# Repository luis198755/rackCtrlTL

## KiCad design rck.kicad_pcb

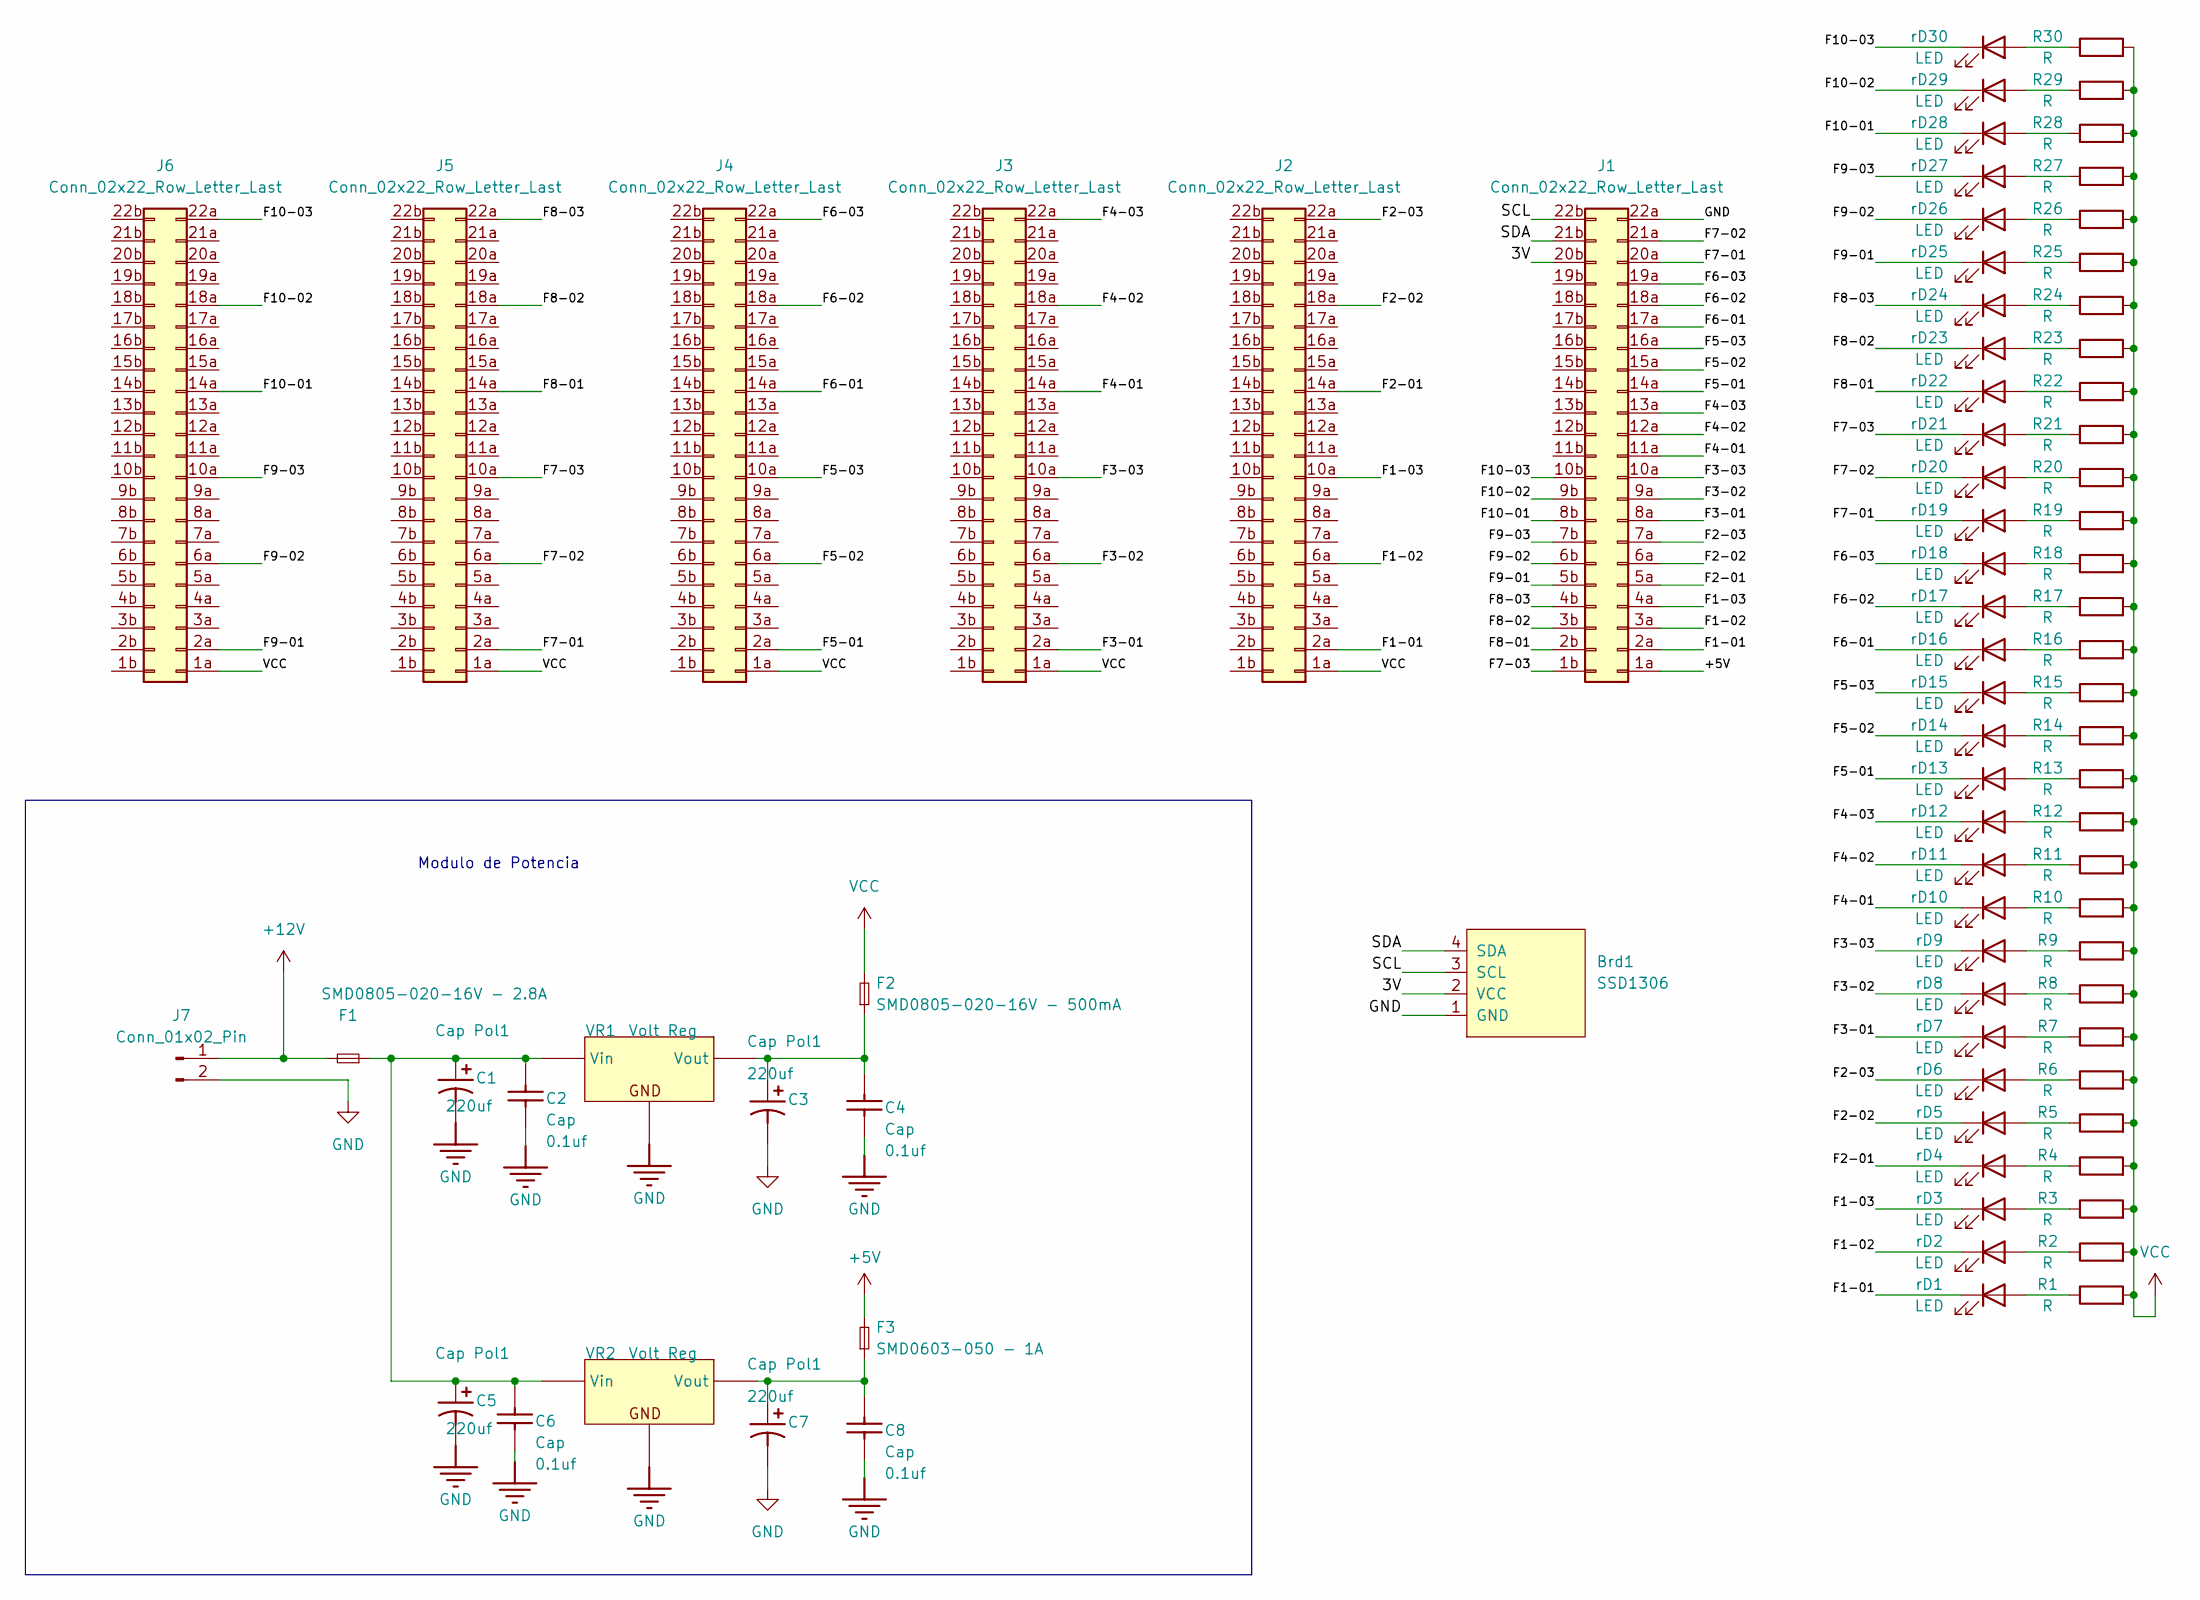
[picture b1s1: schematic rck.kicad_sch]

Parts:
Brd1: SSD1306; 128x64OLED
C1, C3, C5, C7: Cap Pol1; CP_Elec_5x5.9
C2, C4, C6, C8: Cap; C_1210_3225Metric
F1: SMD0805-020-16V - 2.8A; Fuse_0805_2012Metric
F2: SMD0805-020-16V - 500mA; Fuse_0805_2012Metric
F3: SMD0603-050 - 1A; Fuse_0603_1608Metric
J1, J2, J3, J4, J5, J6: Conn_02x22_Row_Letter_Last; Edac_22x2_3.96
J7: Conn_01x02_Pin; PinSocket_1x02_P2.54mm_Vertical
R1, R2, R3, R4, R5, R6, R7, R8, R9, R10, R11, R12, R13, R14, R15, R16, R17, R18, R19, R20, R21, R22, R23, R24, R25, R26, R27, R28, R29, R30: R; R_1206_3216Metric
VR1: Volt Reg; TO-252-3_TabPin2
VR2: Volt Reg; TO-220-3_Vertical
rD1, rD2, rD3, rD4, rD5, rD6, rD7, rD8, rD9, rD10, rD11, rD12, rD13, rD14, rD15, rD16, rD17, rD18, rD19, rD20, rD21, rD22, rD23, rD24, rD25, rD26, rD27, rD28, rD29, rD30: LED; LED_1206_3216Metric

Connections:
+5V: F3.2, J1.1a
+12V: F1.2, J7.1
/3V: Brd1.2 (VCC), J1.20b
/F1-01: J1.2a, J2.2a, rD1.1 (K)
/F1-02: J1.3a, J2.6a, rD2.1 (K)
/F1-03: J1.4a, J2.10a, rD3.1 (K)
/F2-01: J1.5a, J2.14a, rD4.1 (K)
/F2-02: J1.6a, J2.18a, rD5.1 (K)
/F2-03: J1.7a, J2.22a, rD6.1 (K)
/F3-01: J1.8a, J3.2a, rD7.1 (K)
/F3-02: J1.9a, J3.6a, rD8.1 (K)
/F3-03: J1.10a, J3.10a, rD9.1 (K)
/F4-01: J1.11a, J3.14a, rD10.1 (K)
/F4-02: J1.12a, J3.18a, rD11.1 (K)
/F4-03: J1.13a, J3.22a, rD12.1 (K)
/F5-01: J1.14a, J4.2a, rD13.1 (K)
/F5-02: J1.15a, J4.6a, rD14.1 (K)
/F5-03: J1.16a, J4.10a, rD15.1 (K)
/F6-01: J1.17a, J4.14a, rD16.1 (K)
/F6-02: J1.18a, J4.18a, rD17.1 (K)
/F6-03: J1.19a, J4.22a, rD18.1 (K)
/F7-01: J1.20a, J5.2a, rD19.1 (K)
/F7-02: J1.21a, J5.6a, rD20.1 (K)
/F7-03: J1.1b, J5.10a, rD21.1 (K)
/F8-01: J1.2b, J5.14a, rD22.1 (K)
/F8-02: J1.3b, J5.18a, rD23.1 (K)
/F8-03: J1.4b, J5.22a, rD24.1 (K)
/F9-01: J1.5b, J6.2a, rD25.1 (K)
/F9-02: J1.6b, J6.6a, rD26.1 (K)
/F9-03: J1.7b, J6.10a, rD27.1 (K)
/F10-01: J1.8b, J6.14a, rD28.1 (K)
/F10-02: J1.9b, J6.18a, rD29.1 (K)
/F10-03: J1.10b, J6.22a, rD30.1 (K)
/SCL: Brd1.3 (SCL), J1.22b
/SDA: Brd1.4 (SDA), J1.21b
GND: Brd1.1 (GND), C1.2, C2.1, C3.2, C4.1, C5.2, C6.1, C7.2, C8.1, J1.22a, J7.2, VR1.2 (GND), VR2.2 (GND)
unnamed: C1.1, C2.2, C5.1, C6.2, F1.1, VR1.1 (Vin), VR2.1 (Vin)
unnamed: C3.1, C4.2, F2.1, VR1.3 (Vout)
unnamed: C7.1, C8.2, F3.1, VR2.3 (Vout)
unnamed: R1.1, rD1.2 (A)
unnamed: R2.1, rD2.2 (A)
unnamed: R3.1, rD3.2 (A)
unnamed: R4.1, rD4.2 (A)
unnamed: R5.1, rD5.2 (A)
unnamed: R6.1, rD6.2 (A)
unnamed: R7.1, rD7.2 (A)
unnamed: R8.1, rD8.2 (A)
unnamed: R9.1, rD9.2 (A)
unnamed: R10.1, rD10.2 (A)
unnamed: R11.1, rD11.2 (A)
unnamed: R12.1, rD12.2 (A)
unnamed: R13.1, rD13.2 (A)
unnamed: R14.1, rD14.2 (A)
unnamed: R15.1, rD15.2 (A)
unnamed: R16.1, rD16.2 (A)
unnamed: R17.1, rD17.2 (A)
unnamed: R18.1, rD18.2 (A)
unnamed: R19.1, rD19.2 (A)
unnamed: R20.1, rD20.2 (A)
unnamed: R21.1, rD21.2 (A)
unnamed: R22.1, rD22.2 (A)
unnamed: R23.1, rD23.2 (A)
unnamed: R24.1, rD24.2 (A)
unnamed: R25.1, rD25.2 (A)
unnamed: R26.1, rD26.2 (A)
unnamed: R27.1, rD27.2 (A)
unnamed: R28.1, rD28.2 (A)
unnamed: R29.1, rD29.2 (A)
unnamed: R30.1, rD30.2 (A)
VCC: F2.2, J2.1a, J3.1a, J4.1a, J5.1a, J6.1a, R1.2, R2.2, R3.2, R4.2, R5.2, R6.2, R7.2, R8.2, R9.2, R10.2, R11.2, R12.2, R13.2, R14.2, R15.2, R16.2, R17.2, R18.2, R19.2, R20.2, R21.2, R22.2, R23.2, R24.2, R25.2, R26.2, R27.2, R28.2, R29.2, R30.2

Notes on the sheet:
Modulo de Potencia

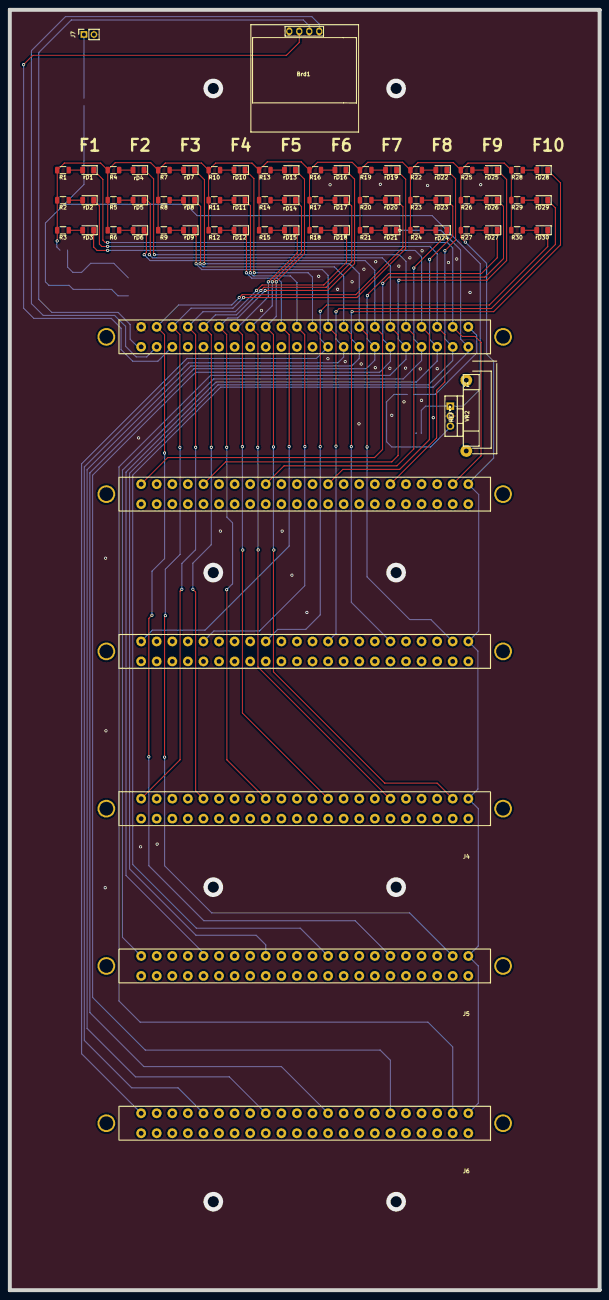
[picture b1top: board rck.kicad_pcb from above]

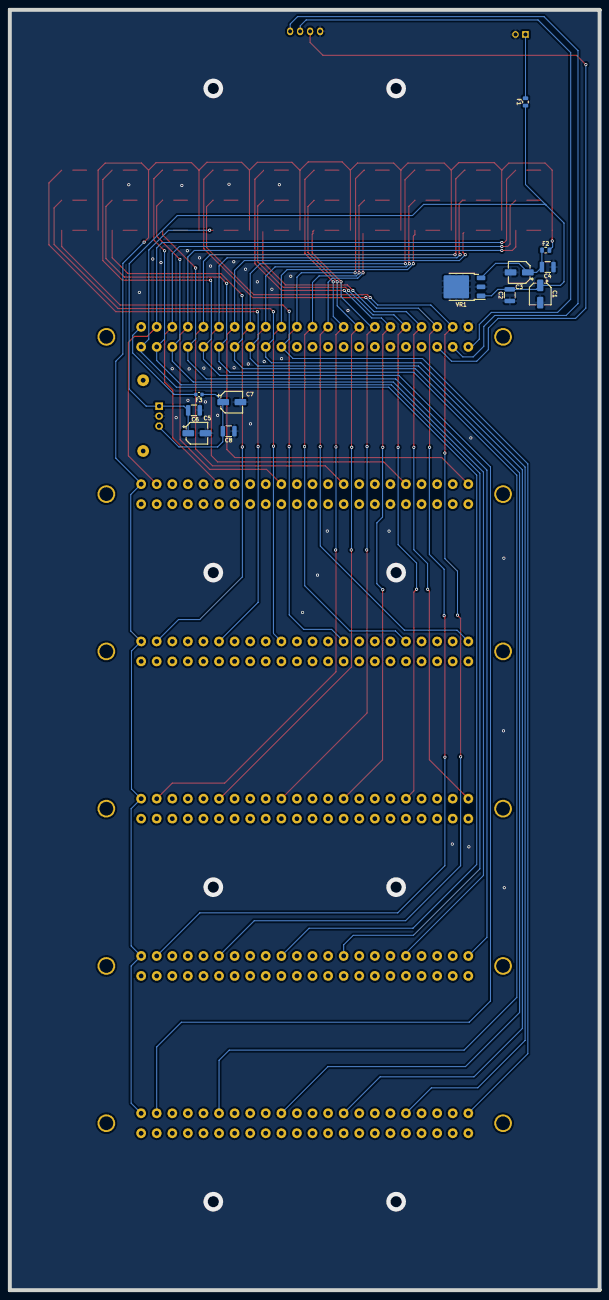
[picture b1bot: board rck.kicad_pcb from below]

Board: 2 copper layers, 150.0 x 325.6 mm, 81 parts (12 on the bottom side), 70 nets.

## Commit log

2024-02-14 V1.0Rack
2024-02-14 V2.0_Rack
2024-02-15 v2Reg12v
2024-02-16 v2Reg12vMolex
2024-02-20 v1.5
2024-03-12 corrección5V
2024-03-28 cambio de 7805
2024-03-29 7805-TO220
2024-05-23 10F Connected
2024-05-23 update 10F
2024-05-23 change page size
2024-05-24 F10 Compleate
2024-05-24 10F Comp
2024-05-24 8 Fases
2024-05-27 6F Complete
2024-05-27 Add .gitignore
2024-05-27 Add Ground plane
2024-05-27 Modify Net-(VR1-Vin)
2024-05-27 Fix route
2024-05-27 Fix routes
2024-05-27 add *.zip to gitignore
2024-05-27 erase zip gerber
2024-05-27 Erase all gerber and drill and add to gitignore
2024-05-27 add zip, grb and dril files to gitignore
2024-05-27 Add zip, gbr and drl files to gitignore
2024-05-27 Add gerber folder
